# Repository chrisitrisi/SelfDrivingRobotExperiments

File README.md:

# SelfDrivingRobotExperiments

Wir verwenden ein vorgegebenes Modellfahrzeug als Basis. Wir entwickeln dafür eine eigene Platine, programmieren die Fahrzeugsoftware neu und erstellen ein eigenes 3D-Modell. Zusätzliche Entfernungssensoren sind eine Option.

| Bereich | Arbeitsstand |
| --- | --- |
| Hardware (Christopher) | [PCB](https://github.com/chrisitrisi/SelfDrivingRobotExperiments/tree/PCB/PCB) enthält KiCad-Projekte, darunter den Liniensensor. |
| Software | [Main_code](https://github.com/chrisitrisi/SelfDrivingRobotExperiments/tree/Main_code), [code](https://github.com/chrisitrisi/SelfDrivingRobotExperiments/tree/code) und [Test](https://github.com/chrisitrisi/SelfDrivingRobotExperiments/tree/Test) enthalten ESP-IDF-Sensorversuche. Den Ausgangsbranch pro Aufgabe im Issue angeben. |
| 3D-Design | [3D_Design](https://github.com/chrisitrisi/SelfDrivingRobotExperiments/tree/3D_Design/3D_Design-Modelling) enthält Fahrzeug- und Gehäusemodelle sowie Exporte. |
| Diplomarbeitsunterlagen | [Dokumentation](https://github.com/chrisitrisi/SelfDrivingRobotExperiments/tree/Dokumentation/Dokumentation) |

## Gemeinsam arbeiten

1. Erstellt ein [Issue](https://github.com/chrisitrisi/SelfDrivingRobotExperiments/issues/new) mit Ziel, Rolle, Ausgangsbranch und einem überprüfbaren Ergebnis. Bei Aufgaben für mehrere Bereiche beschreibt ihr die Teilaufgaben im selben Issue.
2. Lest die aktuelle [AGENTS.md](https://github.com/chrisitrisi/SelfDrivingRobotExperiments/blob/master/AGENTS.md), die [Schnittstellen](https://github.com/chrisitrisi/SelfDrivingRobotExperiments/blob/master/docs/schnittstellen.md) und die neuesten Issue-Kommentare. Die zentralen Dateien liegen auf `master`, auch wenn ihr gerade einen anderen Branch bearbeitet.
3. Erstellt euren Aufgabenbranch vom vereinbarten Fachbranch. Öffnet den Pull Request zurück in diesen Fachbranch und verlinkt das Issue. Änderungen an gemeinsamen Regeln und Schnittstellen gehen in einen eigenen Pull Request gegen `master`.
4. Haltet im Issue fest, was geprüft wurde, was offen ist und von welcher Rolle ihr eine Antwort braucht.

### Projektstart im Terminal

Mit Python 3 und einer über `gh auth login` angemeldeten GitHub CLI könnt ihr im aktualisierten `master`-Checkout den Kontext zu einer Aufgabe anzeigen. Ersetzt 12 durch eine echte Issue-Nummer:

```sh
python tools/projektstart.py 12
```

Das Skript liest Regeln und Schnittstellen von GitHub sowie das Issue mit seinen Kommentaren. Es wechselt keinen Branch. In einem separaten Fachbranch-Checkout könnt ihr das Skript über seinen Pfad im `master`-Checkout starten.

### Prompt für Antigravity, Claude und ChatGPT

> Wir arbeiten in chrisitrisi/SelfDrivingRobotExperiments. Meine Rolle ist [Hardware, Software oder 3D-Design]. Bearbeite Issue #[Nummer]. Lies AGENTS.md und docs/schnittstellen.md vom aktuellen master sowie das Issue mit seinen Kommentaren. Prüfe den dort genannten Fachbranch, bevor du Dateien bearbeitest. Arbeite auf einem Aufgabenbranch und adressiere den Pull Request an den Fachbranch. Teile Ergebnis, Prüfung und offene Fragen im Issue. Falls dir der Zugriff fehlt, benenne die fehlende Datei oder Aktion und liefere einen kopierbaren Entwurf.

Hinterlegt diesen Verweis in Browser-Projekten als Projektanweisung. Öffnet bei lokalen Tools den richtigen Repository-Ordner. Auf älteren Fachbranches können die zentralen Regeldateien fehlen. Gebt den Verweis dann beim Sitzungsstart mit. In Claude-Projekten mit synchronisierten Dateien vor der Arbeit den Stand von `master` aktualisieren und das Issue über ein GitHub-Werkzeug oder als Text bereitstellen.

**Zugriff testen:** Eine Person schreibt ein Prüfwort in ein Test-Issue. Die zweite KI liest es, antwortet im selben Issue und gibt den Kommentarlink zurück. Die dritte KI liest diese Antwort. Damit testet ihr Datei-, Issue- und Kommentarzugriff getrennt.

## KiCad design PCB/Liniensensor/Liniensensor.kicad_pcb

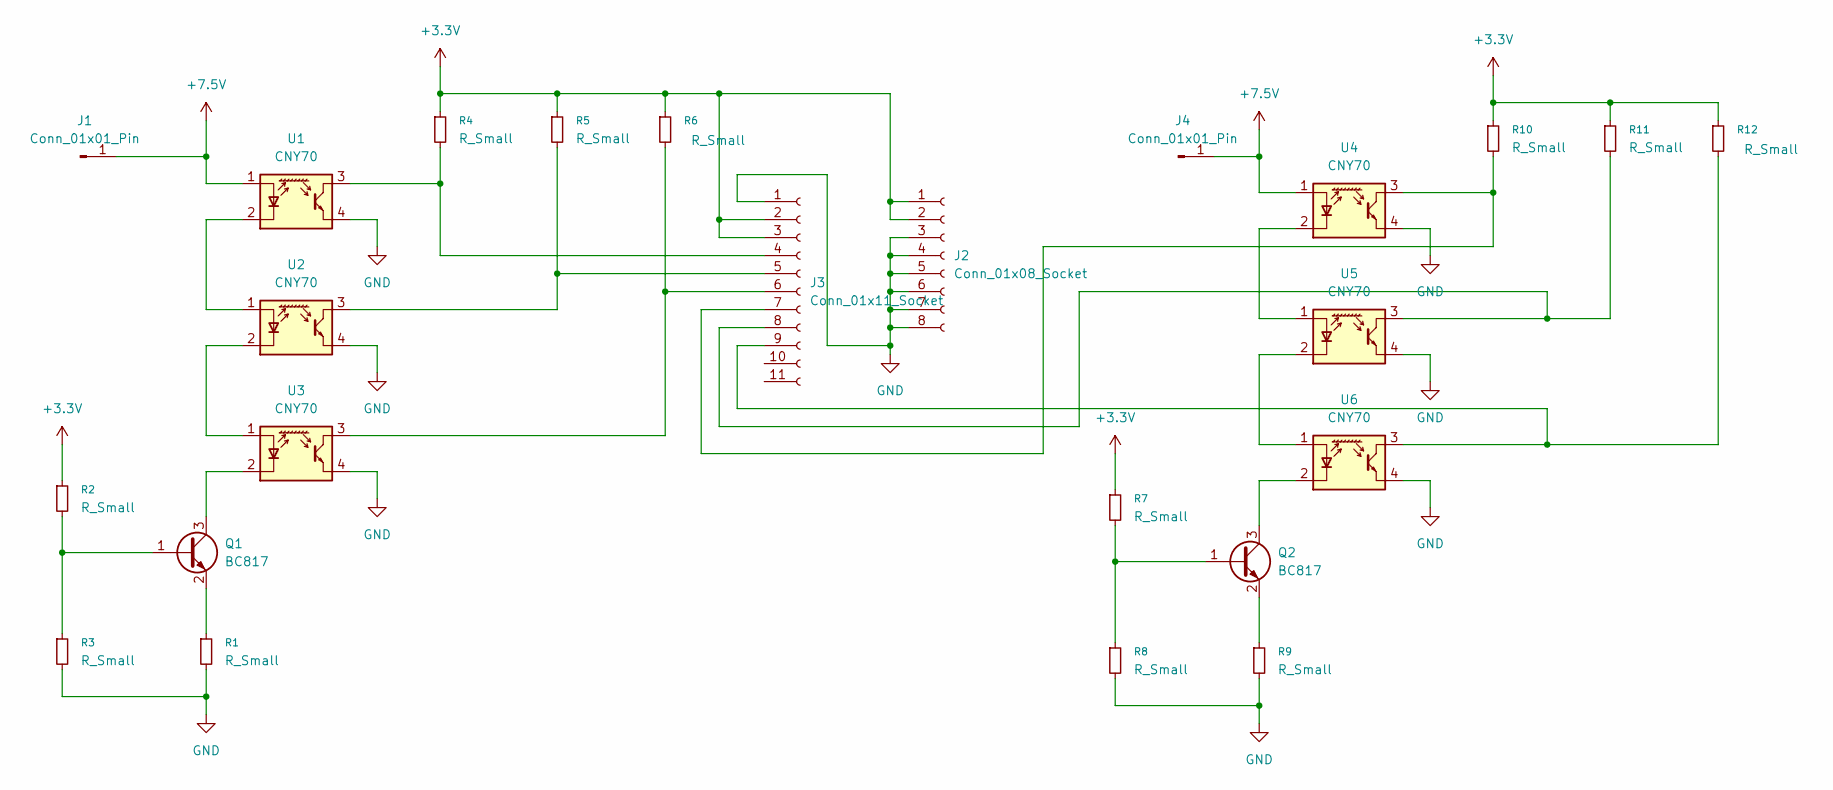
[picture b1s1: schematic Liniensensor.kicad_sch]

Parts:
J1, J4: Conn_01x01_Pin; SolderWire-0.127sqmm_1x01_D0.48mm_OD1mm
J2: Conn_01x08_Socket; PinSocket_1x08_P2.54mm_Vertical
J3: Conn_01x11_Socket; PinSocket_1x11_P2.54mm_Vertical
Q1, Q2: BC817; SOT-23
R1, R2, R3, R7, R8, R9: R_Small; R_0805_2012Metric_Pad1.20x1.40mm_HandSolder
R4, R5, R6, R10, R11, R12: R_Small; R_Axial_DIN0207_L6.3mm_D2.5mm_P7.62mm_Horizontal
U1, U2, U3, U4, U5, U6: CNY70; Vishay_CNY70

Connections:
+3.3V: J2.1, J2.2, J3.2, J3.3, R2.1, R4.1, R5.1, R6.1, R7.1, R10.1, R11.1, R12.1
+7.5V: J1.1, J4.1, U1.1 (A), U4.1 (A)
GND: J2.3, J2.4, J2.5, J2.6, J2.7, J2.8, J3.1, R1.2, R3.2, R8.2, R9.2, U1.4 (E), U2.4 (E), U3.4 (E), U4.4 (E), U5.4 (E), U6.4 (E)
unnamed: J3.4, R4.2, U1.3 (C)
unnamed: J3.5, R5.2, U2.3 (C)
unnamed: J3.6, R6.2, U3.3 (C)
unnamed: J3.7, R10.2, U4.3 (C)
unnamed: J3.8, R11.2, U5.3 (C)
unnamed: J3.9, R12.2, U6.3 (C)
unnamed: Q1.1 (B), R2.2, R3.1
unnamed: Q1.3 (C), U3.2 (K)
unnamed: Q1.2 (E), R1.1
unnamed: Q2.1 (B), R7.2, R8.1
unnamed: Q2.3 (C), U6.2 (K)
unnamed: Q2.2 (E), R9.1
unnamed: U1.2 (K), U2.1 (A)
unnamed: U2.2 (K), U3.1 (A)
unnamed: U4.2 (K), U5.1 (A)
unnamed: U5.2 (K), U6.1 (A)

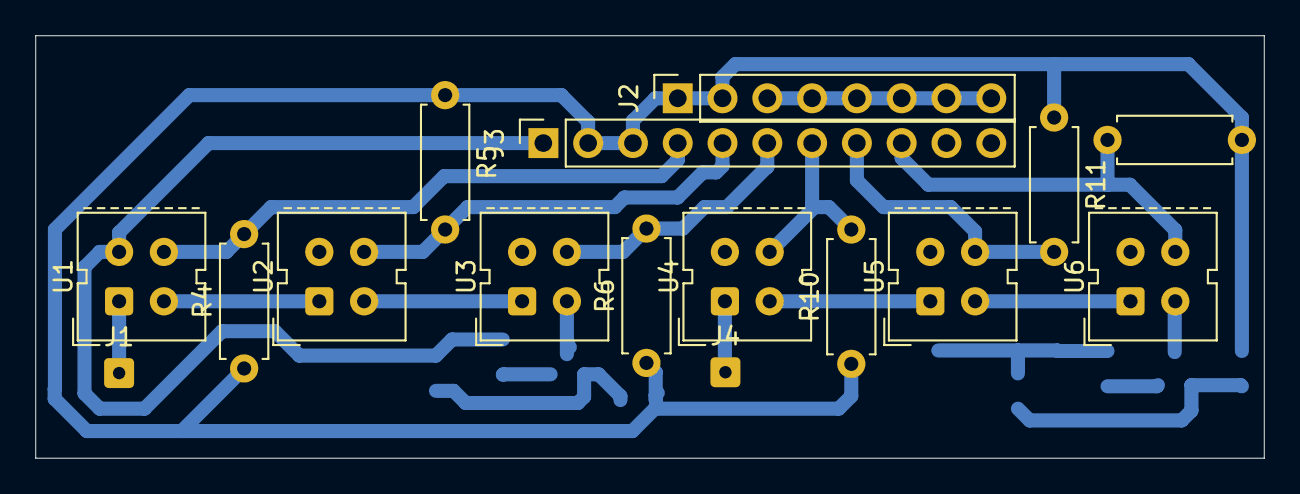
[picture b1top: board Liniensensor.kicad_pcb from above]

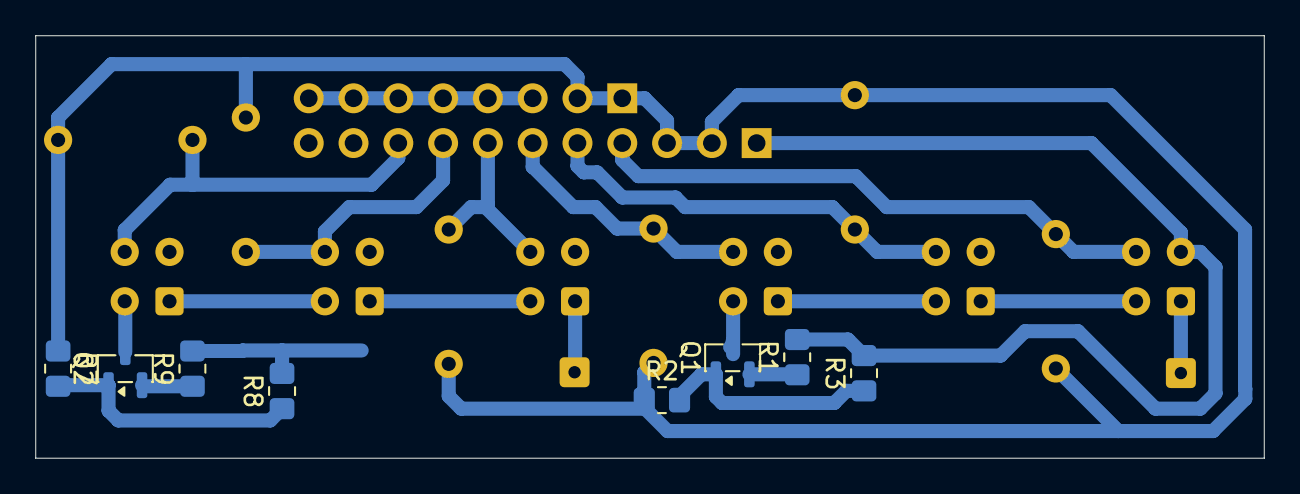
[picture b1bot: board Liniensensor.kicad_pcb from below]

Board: 2 copper layers, 69.7 x 24.0 mm, 24 parts (8 on the bottom side), 19 nets.
